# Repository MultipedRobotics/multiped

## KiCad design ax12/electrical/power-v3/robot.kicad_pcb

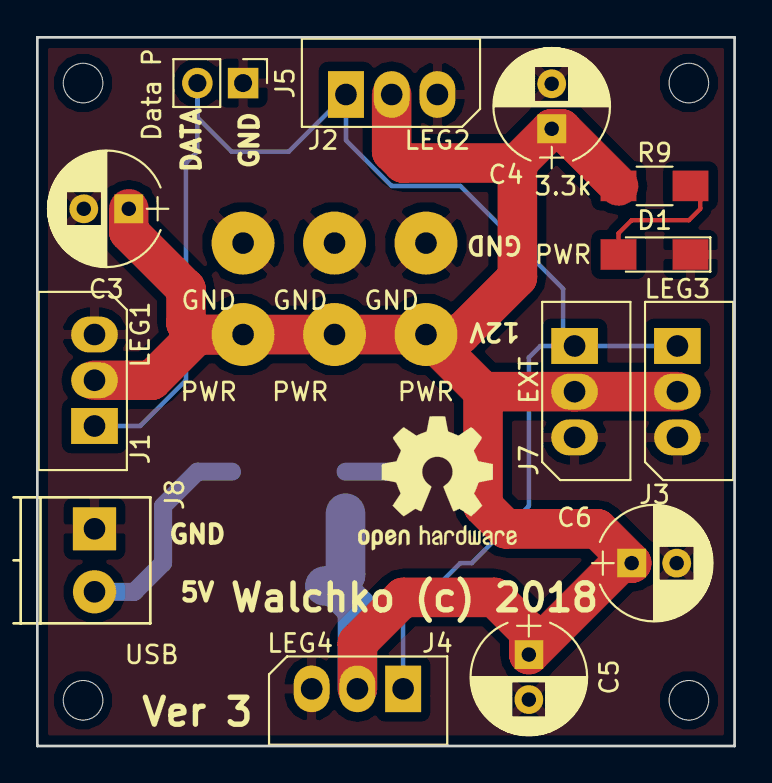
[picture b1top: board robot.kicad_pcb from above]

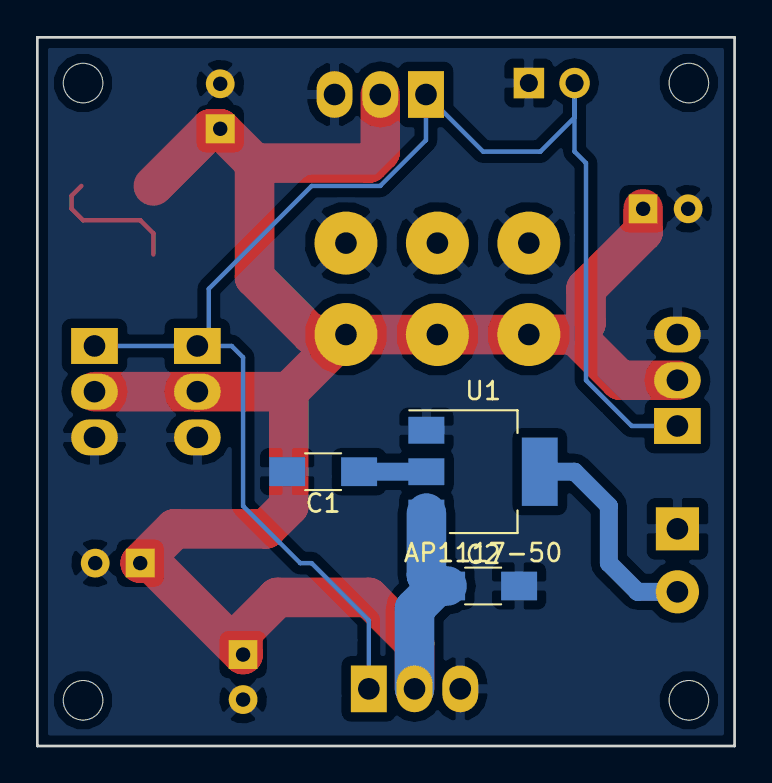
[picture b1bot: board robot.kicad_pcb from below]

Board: 2 copper layers, 38.7 x 39.4 mm, 22 parts (3 on the bottom side), 5 nets.

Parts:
C1, C2: C; C_1206_HandSoldering
C3, C4, C5, C6: .1; CP_Radial_D6.3mm_P2.50mm
D1: PWR; LED_1206_HandSoldering
J1: LEG1; Molex_SPOX-5267_22-03-5035_03x2.54mm_Straight
J2: LEG2; Molex_SPOX-5267_22-03-5035_03x2.54mm_Straight
J3: LEG3; Molex_SPOX-5267_22-03-5035_03x2.54mm_Straight
J4: LEG4; Molex_SPOX-5267_22-03-5035_03x2.54mm_Straight
J5: Data P; Pin_Header_Straight_1x02_Pitch2.54mm
J6, J9, J10: PWR; SolderWirePad_single_1-2mmDrill
J7: EXT; Molex_SPOX-5267_22-03-5035_03x2.54mm_Straight
J8: USB; TerminalBlock_Phoenix_PT-3.5mm_2pol
J11, J12, J13: GND; SolderWirePad_single_1-2mmDrill
R9: 3.3k; R_1206_HandSoldering
U1: AP1117-50; SOT-223-3_TabPin2

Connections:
+5V: C1.1, J8.2, U1.2
+12V: C2.1, C3.1, C4.1, C5.1, C6.1, J1.2, J2.2, J3.2, J4.2, J6.1, J7.2, J9.1, J10.1, R9.1, U1.3
DATA: J1.1, J2.1, J3.1, J4.1, J5.2, J7.1
GND: C1.2, C2.2, C3.2, C4.2, C5.2, C6.2, D1.1, J1.3, J2.3, J3.3, J4.3, J5.1, J7.3, J8.1, J11.1, J12.1, J13.1, U1.1
unnamed: D1.2, R9.2

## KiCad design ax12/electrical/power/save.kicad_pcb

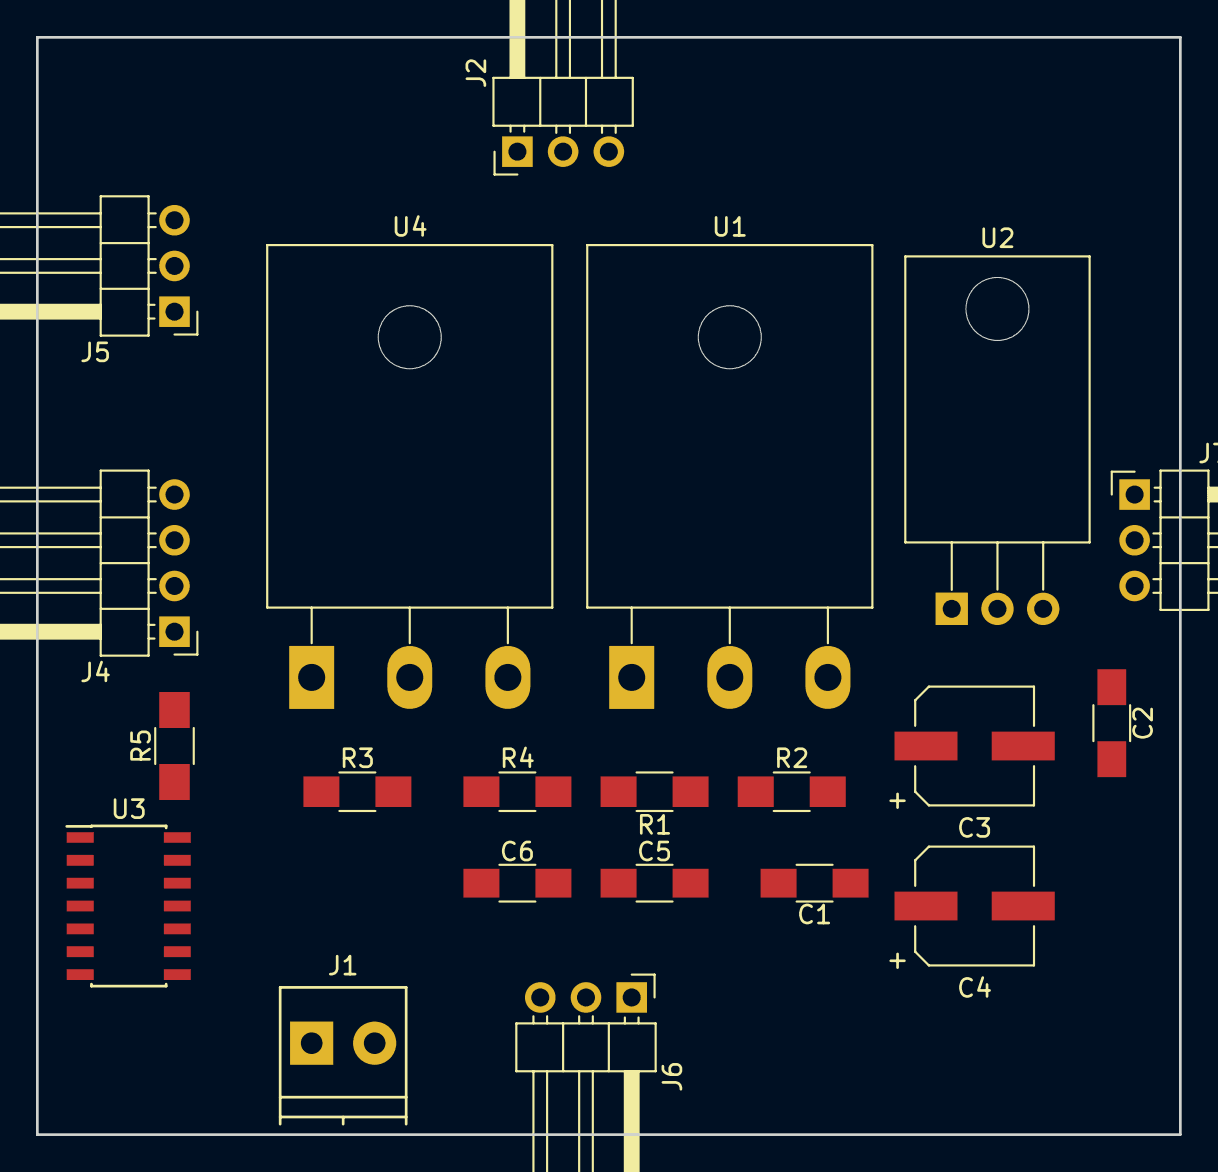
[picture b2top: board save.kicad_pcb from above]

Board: 2 copper layers, 63.5 x 61.0 mm, 21 parts (0 on the bottom side), 12 nets, no tracks yet.

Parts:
C1, C2, C5, C6: C; C_1206_HandSoldering
C3, C4: .1; CP_Elec_6.3x4.5
J1: 12V; TerminalBlock_Phoenix_PT-3.5mm_2pol
J2: LEG1; Pin_Header_Angled_1x03_Pitch2.54mm
J4: Serial; Pin_Header_Angled_1x04_Pitch2.54mm
J5: LEG2; Pin_Header_Angled_1x03_Pitch2.54mm
J6: LEG3; Pin_Header_Angled_1x03_Pitch2.54mm
J7: LEG4; Pin_Header_Angled_1x03_Pitch2.54mm
R1, R3: 330; R_1206_HandSoldering
R2, R4: 1.8k; R_1206_HandSoldering
R5: 10k; R_1206_HandSoldering
U1: LM317_12; TO-3PB__Horizontal
U2: L7805; TO-220-3_Horizontal
U3: 74LS126; SOIC-14_3.9x8.7mm_Pitch1.27mm
U4: LM317_34; TO-3PB__Horizontal

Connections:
+5V: C2.1, R5.1, U2.3
+12V: C1.1, C5.1, C6.1, J1.2, U1.2, U2.1, U4.2
/DTR: J4.2, U3.1, U3.13
/PWR12: C3.1, J2.2, J5.2, R1.1, U1.3
/PWR34: C4.1, J6.2, J7.2, R3.1, U4.3
/RXO: J4.3, U3.3
/TXI: J4.4, U3.9
DATA: J2.3, J5.3, J6.3, J7.3, U3.2, U3.8
GND: C1.2, C2.2, C3.2, C4.2, C5.2, C6.2, J1.1, J2.1, J4.1, J5.1, J6.1, J7.1, R2.2, R4.2, U2.2, U3.7, U3.12
unnamed: R1.2, R2.1, U1.1
unnamed: R3.2, R4.1, U4.1
unnamed: R5.2, U3.10, U3.11

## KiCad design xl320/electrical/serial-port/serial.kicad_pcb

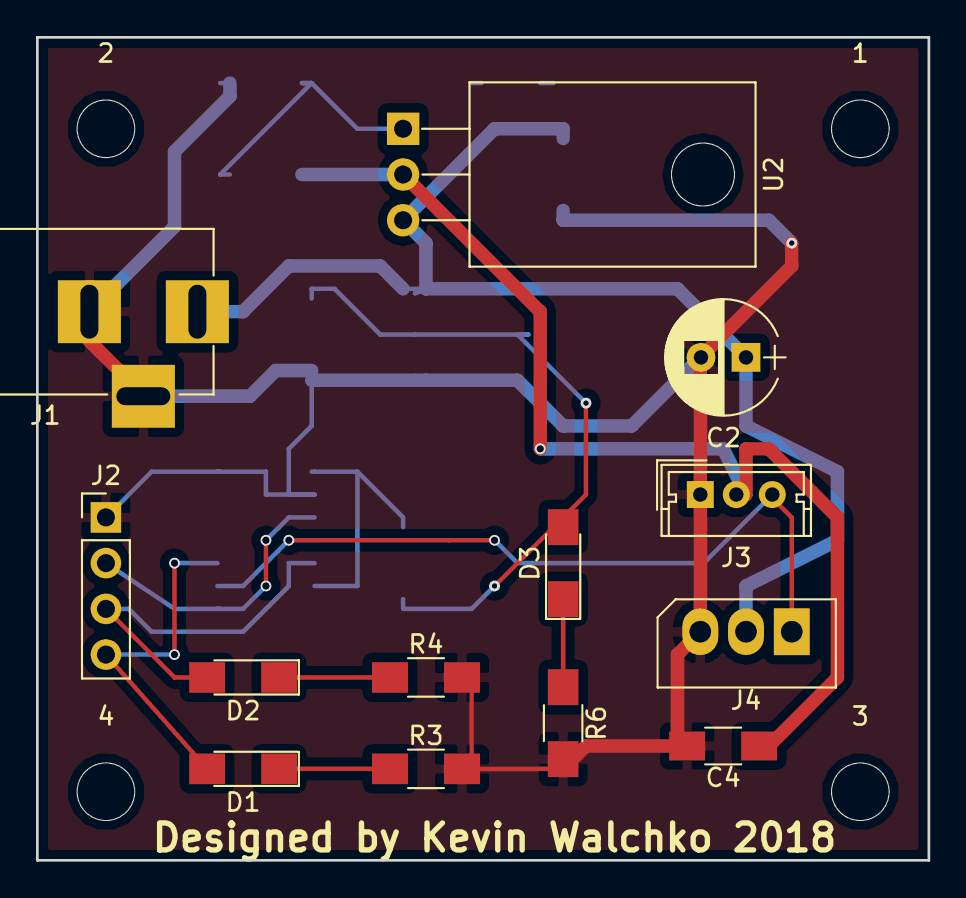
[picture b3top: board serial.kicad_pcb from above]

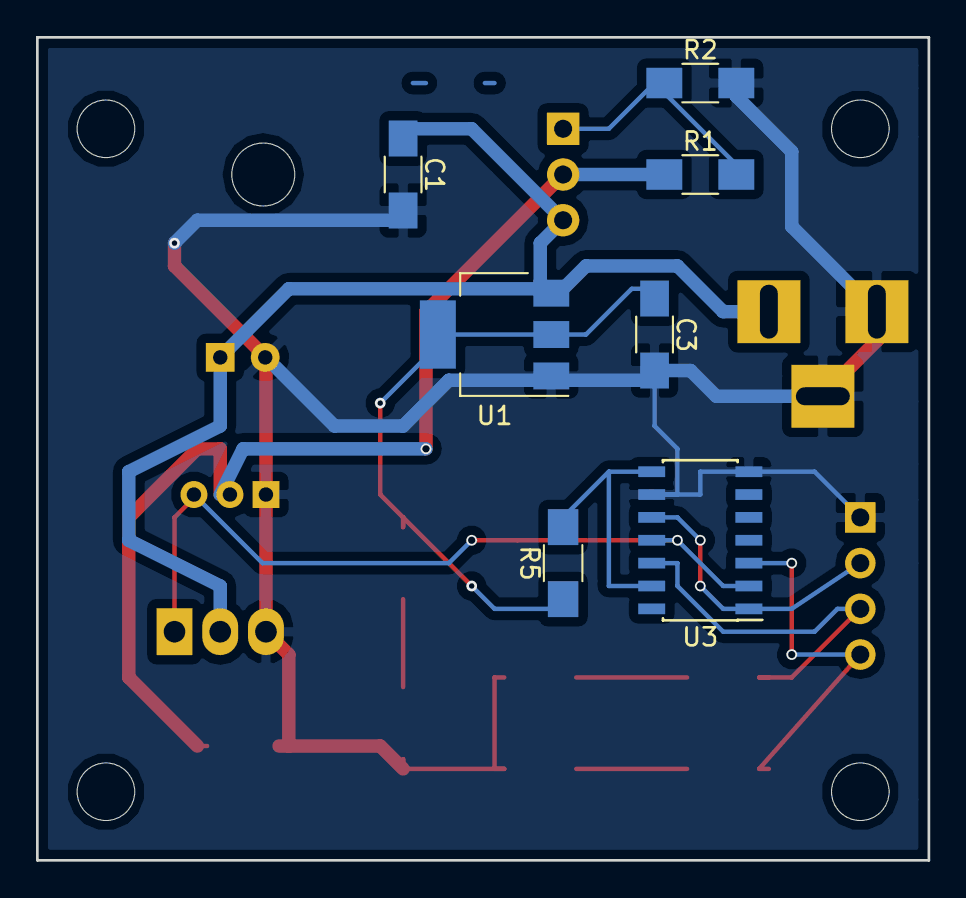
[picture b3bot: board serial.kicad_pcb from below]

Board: 2 copper layers, 49.5 x 45.7 mm, 24 parts (7 on the bottom side), 13 nets.

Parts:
1, 2, 3, 4: MountingHole_3.2mm_M3
C1, C3, C4: .1; C_1206_HandSoldering
C2: 10; CP_Radial_D6.3mm_P2.50mm
D1: RX; LED_1206_HandSoldering
D2: TX; LED_1206_HandSoldering
D3: PWR; LED_1206_HandSoldering
J1: 12V Pwr; BARREL_JACK
J2: Serial 5V; Pin_Header_Straight_1x04_Pitch2.54mm
J3: XL-320; Molex_MicroLatch-53253-0370_03x2.00mm_Straight
J4: AX-12A; Molex_SPOX-5267_22-03-5035_03x2.54mm_Straight
R1, R3, R4, R6: 330; R_1206_HandSoldering
R2: 1.8k; R_1206_HandSoldering
R5: 10k; R_1206_HandSoldering
U1: AP1117-50; SOT-223-3_TabPin2
U2: LM317; TO-220-3_Horizontal
U3: 74LS126; SOIC-14_3.9x8.7mm_Pitch1.27mm

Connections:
+5V: C3.1, D3.2, R5.1, U1.2
+8V: C4.1, J3.2, R1.1, U2.2
+12V: C1.1, C2.1, J1.1, J4.2, U1.3, U2.3
DATA: J3.3, J4.1, U3.2, U3.11
DTR: J2.2, U3.1, U3.10
GND: C1.2, C2.2, C3.2, C4.2, J1.2, J1.3, J2.1, J3.1, J4.3, R2.2, R3.2, R4.2, R6.2, U1.1, U3.7, U3.9
unnamed: D1.1, R3.1
unnamed: D2.1, R4.1
unnamed: D3.1, R6.1
unnamed: R1.2, R2.1, U2.1
unnamed: R5.2, U3.8, U3.13
RXI: D1.2, J2.4, U3.3
TXO: D2.2, J2.3, U3.12

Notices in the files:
ax12/electrical/power-v3/robot.kicad_pcb:
Walchko (c) 2018
